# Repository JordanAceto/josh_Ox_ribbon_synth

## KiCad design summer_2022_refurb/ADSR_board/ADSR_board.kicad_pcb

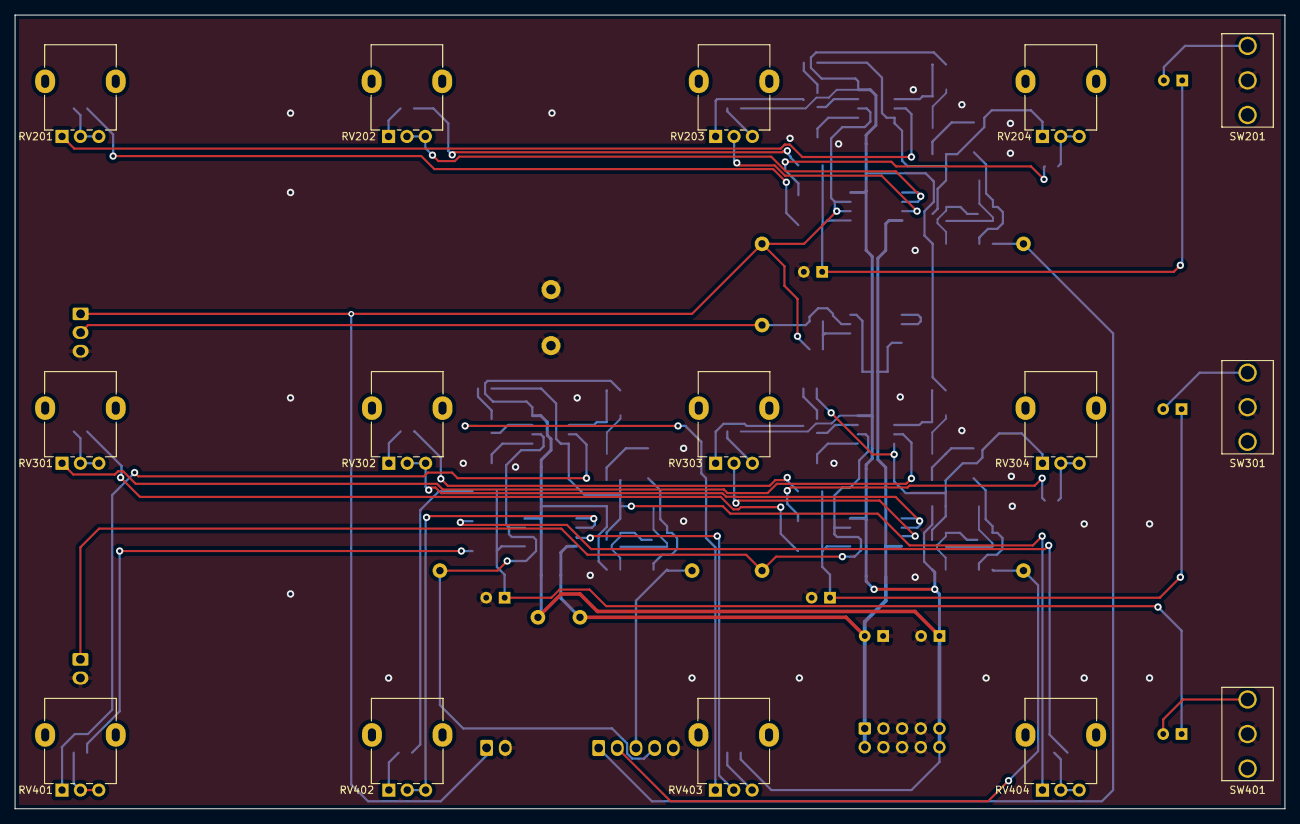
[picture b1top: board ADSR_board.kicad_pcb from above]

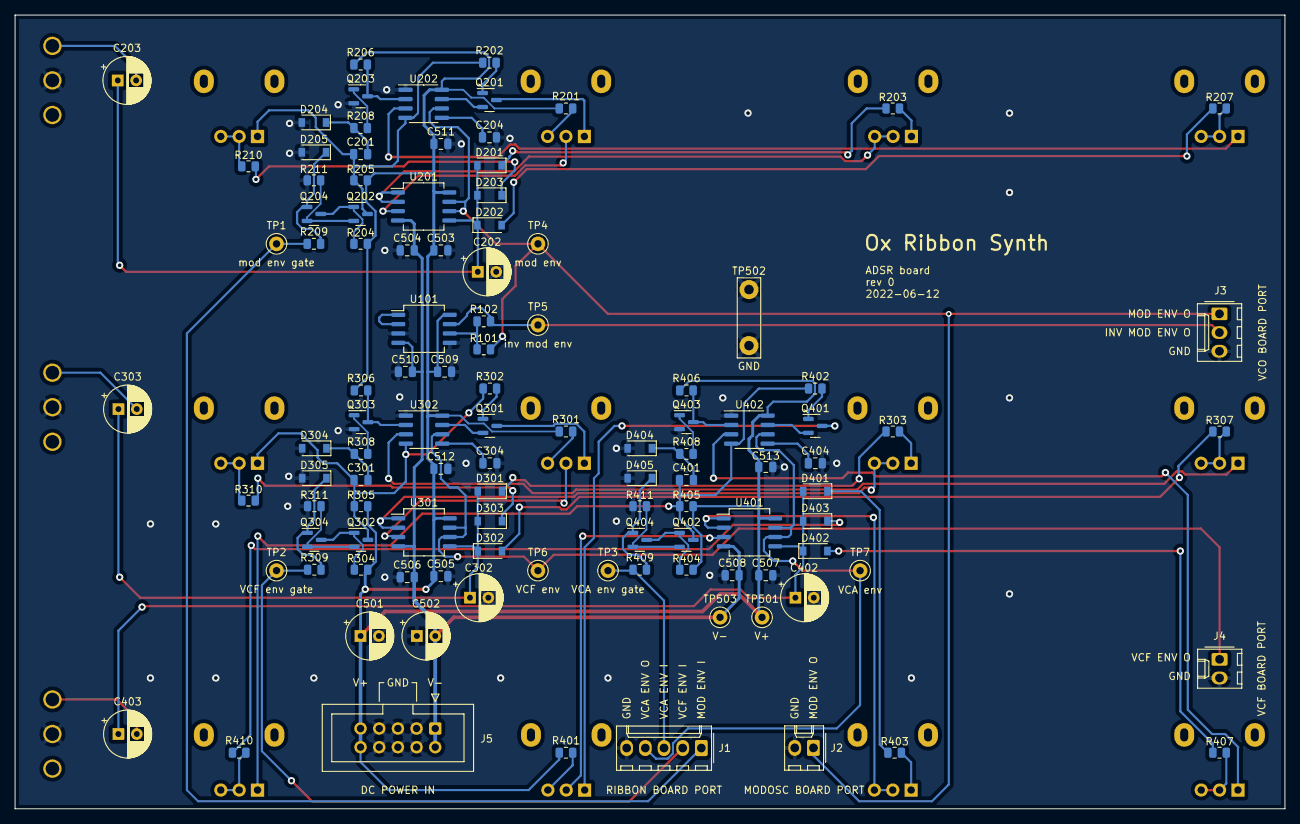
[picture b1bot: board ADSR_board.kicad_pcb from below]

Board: 2 copper layers, 172.7 x 107.9 mm, 124 parts (109 on the bottom side), 81 nets.

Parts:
C201, C204, C301, C304, C401, C404: 10n; C_0805_2012Metric
C202, C302, C402: 2u2; CP_Radial_D6.3mm_P2.50mm
C203, C303, C403: 22u; CP_Radial_D6.3mm_P2.50mm
C501, C502: 10u; CP_Radial_D6.3mm_P2.50mm
C503, C504, C505, C506, C507, C508, C509, C510, C511, C512, C513: 100n; C_0805_2012Metric
D201, D202, D203, D204, D205, D301, D302, D303, D304, D305, D401, D402, D403, D404, D405: 1N4148W; D_SOD-123
J1: ribbon_port; Molex_KK-254_AE-6410-05A_1x05_P2.54mm_Vertical
J2: modosc_port; Molex_KK-254_AE-6410-02A_1x02_P2.54mm_Vertical
J3: VCO_port; Molex_KK-254_AE-6410-03A_1x03_P2.54mm_Vertical
J4: VCF_port; Molex_KK-254_AE-6410-02A_1x02_P2.54mm_Vertical
J5: power_entry; IDC-Header_2x05_P2.54mm_Vertical
Q201, Q301, Q401: 2N7002; SOT-23
Q202, Q203, Q204, Q302, Q303, Q304, Q402, Q403, Q404: MMBT3904; SOT-23
R101, R102, R209, R309, R409: 100k; R_0805_2012Metric
R201, R301, R401: 4k7; R_0805_2012Metric
R202, R302, R402: 1M; R_0805_2012Metric
R203, R207, R210, R303, R307, R310, R403, R407, R410: R; R_0805_2012Metric
R204, R205, R206, R208, R304, R305, R306, R308, R404, R405, R406, R408: 10k; R_0805_2012Metric
R211, R311, R411: 22; R_0805_2012Metric
RV201, RV202, RV204, RV301, RV302, RV304, RV401, RV402, RV404: 500kA; Potentiometer_Alpha_RD901F-40-00D_Single_Vertical
RV203, RV303, RV403: 10k; Potentiometer_Alpha_RD901F-40-00D_Single_Vertical
SW201, SW301, SW401: SW_SPDT; SPDT_mini_toggle
TP1: mod env gate; TestPoint_Keystone_5000-5004_Miniature
TP2: VCF env gate; TestPoint_Keystone_5000-5004_Miniature
TP3: VCA env gate; TestPoint_Keystone_5000-5004_Miniature
TP4: mod env; TestPoint_Keystone_5000-5004_Miniature
TP5: inv mod env; TestPoint_Keystone_5000-5004_Miniature
TP6: VCF env; TestPoint_Keystone_5000-5004_Miniature
TP7: VCA env; TestPoint_Keystone_5000-5004_Miniature
TP501: V+; TestPoint_Keystone_5000-5004_Miniature
TP502: GND; TestPoint_Bridge_Pitch7.62mm_Drill1.3mm
TP503: V-; TestPoint_Keystone_5000-5004_Miniature
U101, U201, U301, U401: TL072; SO-8_5.3x6.2mm_P1.27mm
U202, U302, U402: LM555xM; SOIC-8_3.9x4.9mm_P1.27mm

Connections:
+15V: C501.1, C503.1, C505.1, C507.1, C509.1, C511.1, C512.1, C513.1, J5.9, J5.10, R201.1, R204.1, R205.1, R206.1, R301.1, R304.1, R305.1, R306.1, R401.1, R404.1, R405.1, R406.1, TP501.1, U101.8 (V+), U201.8 (V+), U202.8 (VCC), U301.8 (V+), U302.8 (VCC), U401.8 (V+), U402.8 (VCC)
-15V: C502.2, C504.2, C506.2, C508.2, C510.2, J5.1, J5.2, TP503.1, U101.4 (V-), U201.4 (V-), U301.4 (V-), U401.4 (V-)
/VCA_ADSR/GATE: J1.3, R409.1, TP3.1
/VCA_ENV: J1.4, TP7.1, U401.6 (-), U401.7, U402.6 (THR)
/VCF_ADSR/GATE: J1.2, R309.1, TP2.1
/VCF_ADSR/OUT: J4.1, TP6.1, U301.6 (-), U301.7, U302.6 (THR)
/modulation_ADSR/GATE: J1.1, R209.1, TP1.1
/modulation_ADSR/OUT: J2.1, J3.1, R101.1, TP4.1, U201.6 (-), U201.7, U202.6 (THR)
GND: C202.2, C204.2, C302.2, C304.2, C402.2, C404.2, C501.2, C502.1, C503.2, C504.1, C505.2, C506.1, C507.2, C508.1, C509.2, C510.1, C511.2, C512.2, C513.2, D204.2 (A), D205.2 (A), D304.2 (A), D305.2 (A), D404.2 (A), D405.2 (A), J1.5, J2.2, J3.3, J4.2, J5.3, J5.4, J5.5, J5.6, J5.7, J5.8, Q203.2 (E), Q303.2 (E), Q403.2 (E), R211.2, R311.2, R411.2, SW201.2 (B), SW301.2 (B), SW401.2 (B), TP502.1, U101.3 (+), U101.5 (+), U202.1 (GND), U302.1 (GND), U402.1 (GND)
unnamed: C201.1, Q202.3 (C), R202.1, R205.2, RV204.1, U202.4 (R)
unnamed: C201.2, D204.1 (K), R208.1
unnamed: C202.1, C203.1, D201.2 (A), D202.1 (K), D203.2 (A), U201.5 (+)
unnamed: C203.2, SW201.3 (C)
unnamed: C204.1, U202.5 (CV)
unnamed: C301.1, Q302.3 (C), R302.1, R305.2, RV304.1, U302.4 (R)
unnamed: C301.2, D304.1 (K), R308.1
unnamed: C302.1, C303.1, D301.2 (A), D302.1 (K), D303.2 (A), U301.5 (+)
unnamed: C303.2, SW301.3 (C)
unnamed: C304.1, U302.5 (CV)
unnamed: C401.1, Q402.3 (C), R402.1, R405.2, RV404.1, U402.4 (R)
unnamed: C401.2, D404.1 (K), R408.1
unnamed: C402.1, C403.1, D401.2 (A), D402.1 (K), D403.2 (A), U401.5 (+)
unnamed: C403.2, SW401.3 (C)
unnamed: C404.1, U402.5 (CV)
unnamed: D201.1 (K), R203.2
unnamed: D202.2 (A), R207.2
unnamed: D203.1 (K), R210.1
unnamed: D205.1 (K), Q204.1 (B), R209.2
unnamed: D301.1 (K), R303.2
unnamed: D302.2 (A), R307.2
unnamed: D303.1 (K), R310.1
unnamed: D305.1 (K), Q304.1 (B), R309.2
unnamed: D401.1 (K), R403.2
unnamed: D402.2 (A), R407.2
unnamed: D403.1 (K), R410.1
unnamed: D405.1 (K), Q404.1 (B), R409.2
unnamed: Q201.1 (G), R202.2
unnamed: Q201.2 (S), U202.7 (DIS)
unnamed: Q201.3 (D), RV203.1
unnamed: Q202.1 (B), Q204.3 (C), R204.2
unnamed: Q202.2 (E), Q204.2 (E), R211.1
unnamed: Q203.1 (B), R208.2
unnamed: Q203.3 (C), R206.2, U202.2 (TR)
unnamed: Q301.1 (G), R302.2
unnamed: Q301.2 (S), U302.7 (DIS)
unnamed: Q301.3 (D), RV303.1
unnamed: Q302.1 (B), Q304.3 (C), R304.2
unnamed: Q302.2 (E), Q304.2 (E), R311.1
unnamed: Q303.1 (B), R308.2
unnamed: Q303.3 (C), R306.2, U302.2 (TR)
unnamed: Q401.1 (G), R402.2
unnamed: Q401.2 (S), U402.7 (DIS)
unnamed: Q401.3 (D), RV403.1
unnamed: Q402.1 (B), Q404.3 (C), R404.2
unnamed: Q402.2 (E), Q404.2 (E), R411.1
unnamed: Q403.1 (B), R408.2
unnamed: Q403.3 (C), R406.2, U402.2 (TR)
unnamed: R101.2, R102.1, U101.6 (-)
unnamed: J3.2, R102.2, TP5.1, U101.7
unnamed: R201.2, RV203.3
unnamed: R203.1, RV202.1
unnamed: R207.1, RV201.2, RV201.3
unnamed: R210.2, RV204.2, RV204.3
unnamed: R301.2, RV303.3
unnamed: R303.1, RV302.1
unnamed: R307.1, RV301.2, RV301.3
unnamed: R310.2, RV304.2, RV304.3
unnamed: R401.2, RV403.3
unnamed: R403.1, RV402.1
unnamed: R407.1, RV401.2, RV401.3
unnamed: R410.2, RV404.2, RV404.3
unnamed: RV201.1, U202.3 (Q)
unnamed: RV202.2, RV202.3, U201.1, U201.2 (-)
unnamed: RV203.2, U201.3 (+)
unnamed: RV301.1, U302.3 (Q)
unnamed: RV302.2, RV302.3, U301.1, U301.2 (-)
unnamed: RV303.2, U301.3 (+)
unnamed: RV401.1, U402.3 (Q)
unnamed: RV402.2, RV402.3, U401.1, U401.2 (-)
unnamed: RV403.2, U401.3 (+)
unnamed: U101.1, U101.2 (-)

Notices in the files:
summer_2022_refurb/ADSR_board/ADSR_board.kicad_pcb:
creativecommons.org/licences/by/4.0
license: CC by 4.0
